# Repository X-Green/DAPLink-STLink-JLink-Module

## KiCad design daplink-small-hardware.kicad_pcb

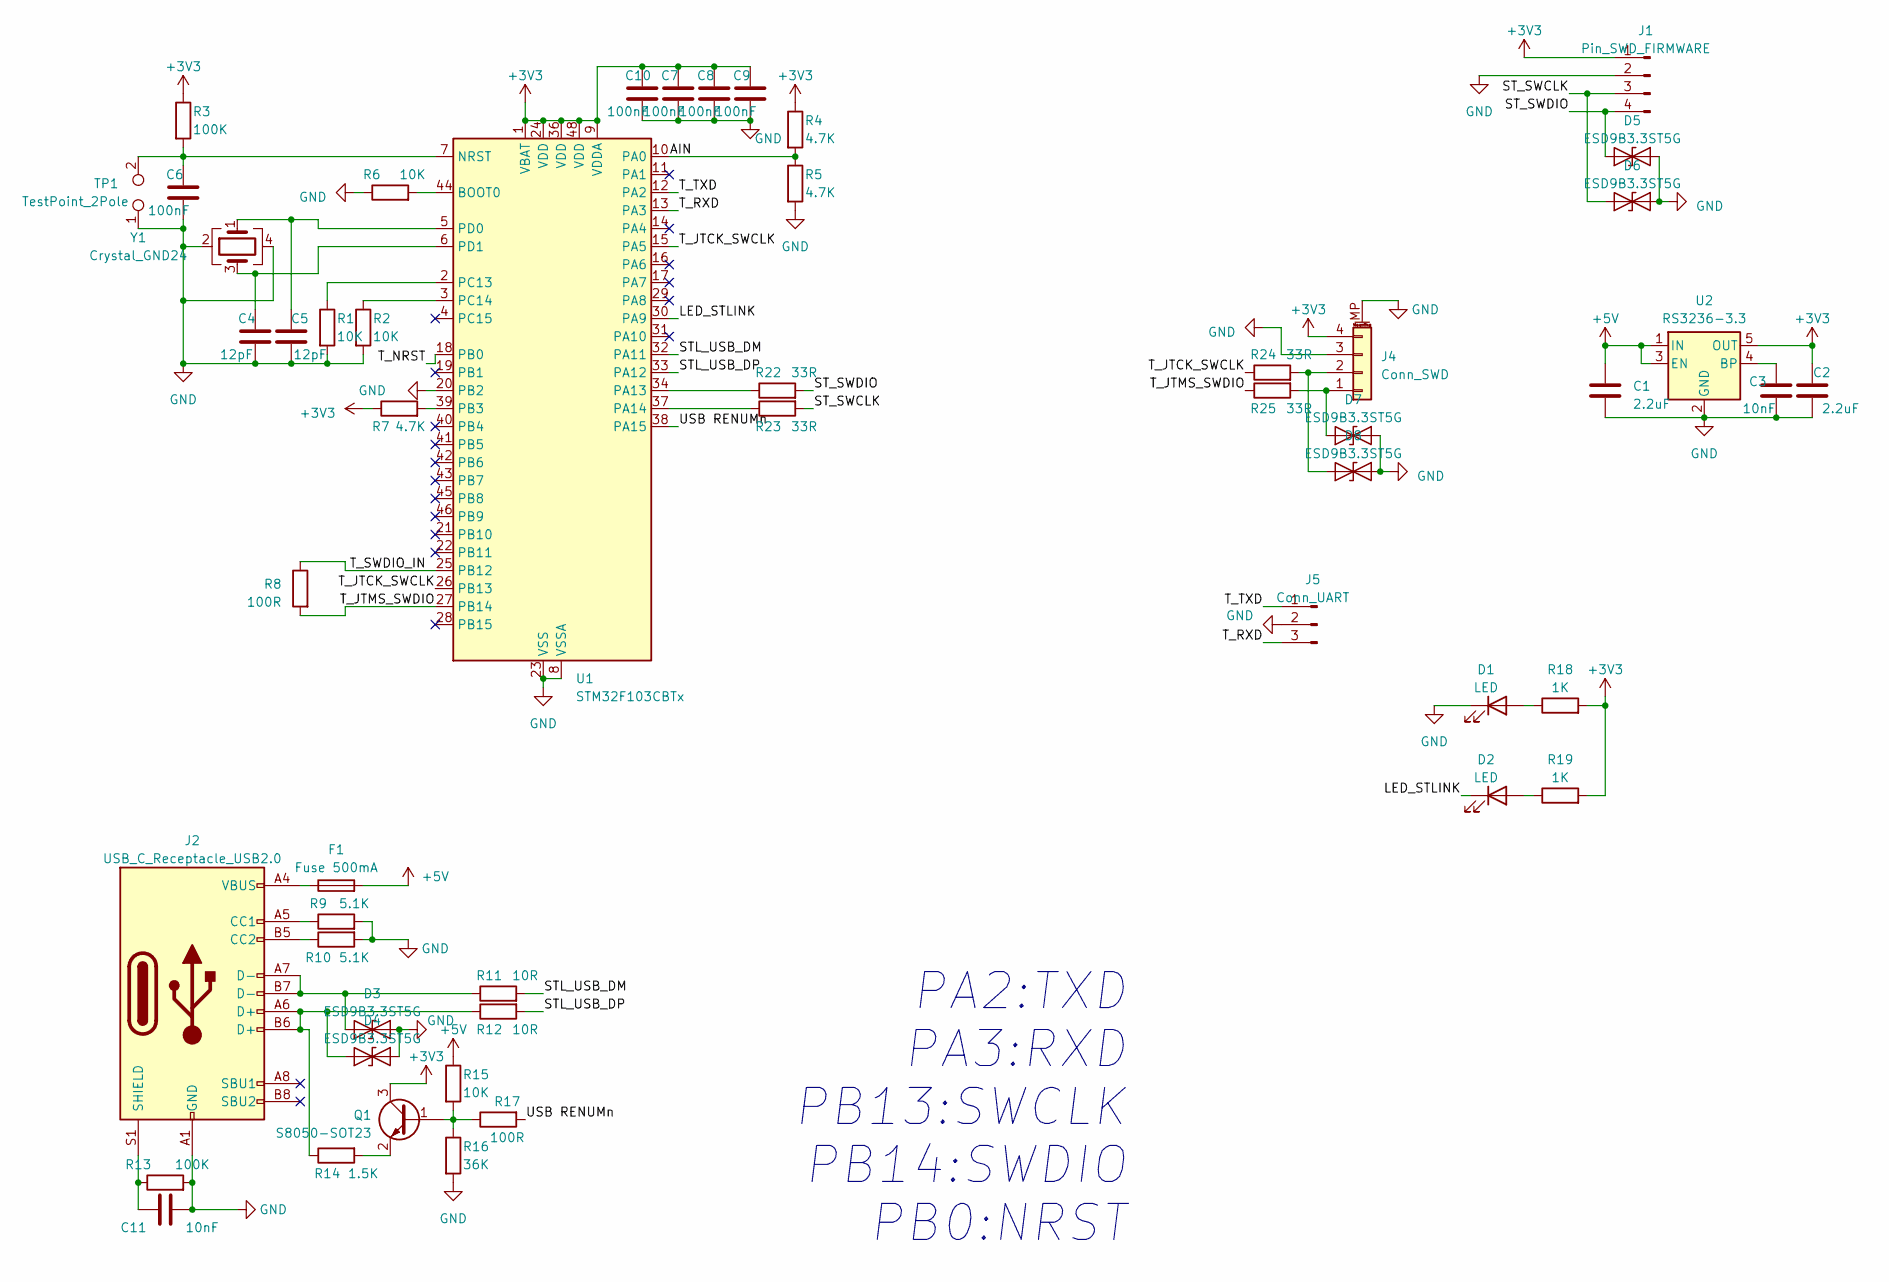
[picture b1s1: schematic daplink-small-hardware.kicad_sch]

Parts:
C1, C2: 2.2uF; C_1206_3216Metric
C3, C11: 10nF; C_0603_1608Metric
C4, C5: 12pF; C_0603_1608Metric
C6, C7, C8, C9, C10: 100nF; C_0603_1608Metric
D1, D2: LED; LED_0603_1608Metric
D3, D4, D5, D6, D7, D8: ESD9B3.3ST5G; D_SOD-323
F1: Fuse 500mA; Fuse_0805_2012Metric
J1: Pin_SWD_FIRMWARE; PinHeader_1x04_P1.27mm_Vertical
J2: USB_C_Receptacle_USB2.0; USB_C_Receptacle_HRO_TYPE-C-31-M-12
J4: Conn_SWD; Molex_PicoBlade_53261-0471_1x04-1MP_P1.25mm_Horizontal
J5: Conn_UART; PinHeader_1x03_P2.54mm_Vertical
Q1: S8050-SOT23; SOT-23
R1, R2, R6, R15: 10K; R_0603_1608Metric
R3, R13: 100K; R_0603_1608Metric
R4, R5, R7: 4.7K; R_0603_1608Metric
R8, R17: 100R; R_0603_1608Metric
R9, R10: 5.1K; R_0603_1608Metric
R11, R12: 10R; R_0603_1608Metric
R14: 1.5K; R_0603_1608Metric
R16: 36K; R_0603_1608Metric
R18, R19: 1K; R_0603_1608Metric
R22, R23, R24, R25: 33R; R_0603_1608Metric
TP1: TestPoint_2Pole; TestPoint_2Pads_Pitch2.54mm_Drill0.8mm
U1: STM32F103CBTx; LQFP-48_7x7mm_P0.5mm
U2: RS3236-3.3; SOT-23-5
Y1: Crystal_GND24; Crystal_SMD_3225-4Pin_3.2x2.5mm

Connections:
+3V3: C2.1, C7.1, C8.1, C9.1, C10.1, J1.1, J4.4, Q1.3 (C), R3.1, R4.1, R7.1, R18.2, R19.2, U1.1 (VBAT), U1.9 (VDDA), U1.24 (VDD), U1.36 (VDD), U1.48 (VDD), U2.5 (OUT)
+5V: C1.1, F1.2, R15.1, U2.1 (IN), U2.3 (EN)
/AIN: R4.2, R5.1, U1.10 (PA0)
/LED_STLINK: D2.1 (K), U1.30 (PA9)
/STL_USB_DM: R11.2, U1.32 (PA11)
/STL_USB_DP: R12.2, U1.33 (PA12)
/ST_SWCLK: D6.1 (A1), J1.3, R23.2
/ST_SWDIO: D5.1 (A1), J1.4, R22.2
/T_JTCK_SWCLK: R24.1, U1.15 (PA5), U1.26 (PB13)
/T_JTMS_SWDIO: R8.2, R25.1, U1.27 (PB14)
/T_NRST: U1.18 (PB0)
/T_RXD: J5.3, U1.13 (PA3)
/T_SWDIO_IN: R8.1, U1.25 (PB12)
/T_TXD: J5.1, U1.12 (PA2)
/USB RENUMn: R17.2, U1.38 (PA15)
GND: C1.2, C2.2, C3.2, C4.2, C5.2, C6.2, C7.2, C8.2, C9.2, C10.2, C11.2, D1.1 (K), D3.2 (A2), D4.2 (A2), D5.2 (A2), D6.2 (A2), D7.2 (A2), D8.2 (A2), J1.2, J2.A1 (GND), J2.A12 (GND), J2.B1 (GND), J2.B12 (GND), J4.3, J4.MP (MountPin), J5.2, R1.2, R2.2, R5.2, R6.1, R9.2, R10.2, R13.2, R16.2, TP1.1, U1.8 (VSSA), U1.20 (PB2), U1.23 (VSS), U1.35 (VSS), U1.47 (VSS), U2.2 (GND), Y1.2, Y1.4
unnamed: D1.2 (A), R18.1
unnamed: D2.2 (A), R19.1
unnamed: D3.1 (A1), J2.A7 (D-), J2.B7 (D-), R11.1
unnamed: D4.1 (A1), J2.A6 (D+), J2.B6 (D+), R12.1, R14.1
unnamed: D7.1 (A1), J4.1, R25.2
unnamed: D8.1 (A1), J4.2, R24.2
unnamed: F1.1, J2.A4 (VBUS), J2.A9 (VBUS), J2.B4 (VBUS), J2.B9 (VBUS)
unnamed: J2.A5 (CC1), R9.1
unnamed: J2.B5 (CC2), R10.1
unnamed: C11.1, J2.S1 (SHIELD), R13.1
unnamed: Q1.1 (B), R15.2, R16.1, R17.1
unnamed: Q1.2 (E), R14.2
unnamed: R6.2, U1.44 (BOOT0)
unnamed: C6.1, R3.2, TP1.2, U1.7 (NRST)
unnamed: R22.1, U1.34 (PA13)
unnamed: R23.1, U1.37 (PA14)
unnamed: R7.2, U1.39 (PB3)
unnamed: R1.1, U1.2 (PC13)
unnamed: R2.1, U1.3 (PC14)
unnamed: C5.1, U1.5 (PD0), Y1.1
unnamed: C4.1, U1.6 (PD1), Y1.3
unnamed: C3.1, U2.4 (BP)

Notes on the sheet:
PA2:TXD PA3:RXD PB13:SWCLK PB14:SWDIO PB0:NRST

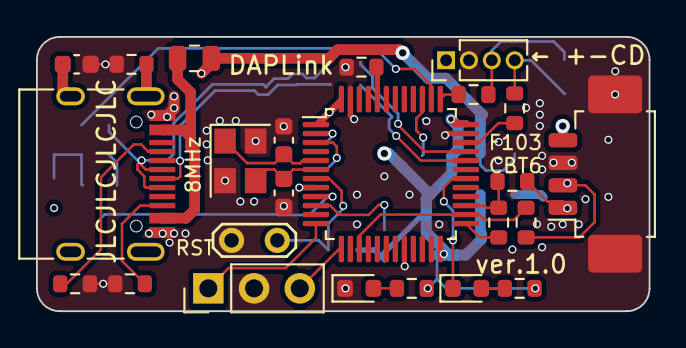
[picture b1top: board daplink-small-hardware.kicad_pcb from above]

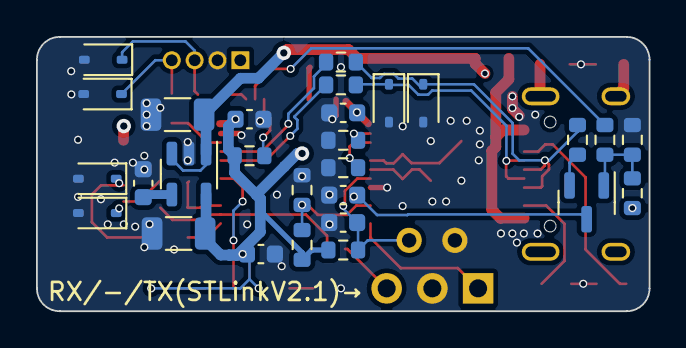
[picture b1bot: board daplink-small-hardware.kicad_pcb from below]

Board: 4 copper layers, 34.0 x 15.2 mm, 52 parts (28 on the bottom side), 37 nets.

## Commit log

2023-05-20 v1.0 done
2023-05-21 Add esd protection; ->Ver1.0.1
